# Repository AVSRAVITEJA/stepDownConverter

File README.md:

# stepDownConverter
In this project I have designed a DC-DC converter that steps down 48V to 28V, 12V and 5V. The pcb designed is used to distribute the input voltage to a camera, gimbal, flight controller and a radio. This pcb is a part of a high altitude surveillance drone with an endurance of 5hrs.
The pcb uses LM2596 IC and XL4015 IC to step down the voltages. Most of the components used are SMD.

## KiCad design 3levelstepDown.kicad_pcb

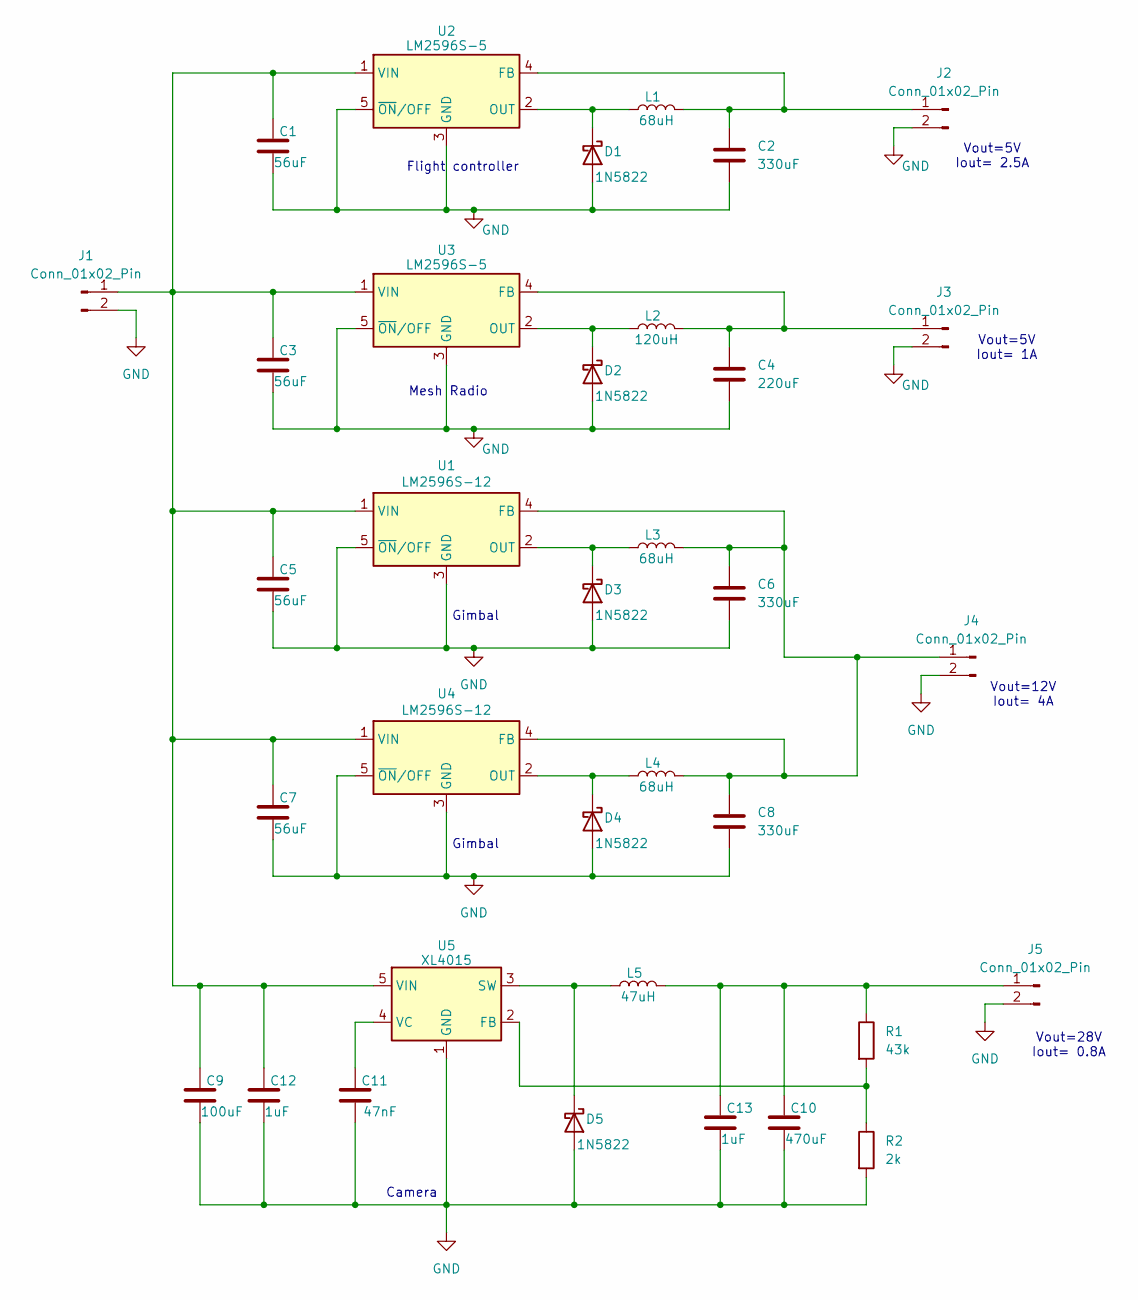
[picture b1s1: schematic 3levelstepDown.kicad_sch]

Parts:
C1, C3, C5, C7: 56uF; CP_Elec_6.3x5.8
C2, C6, C8: 330uF; CP_Elec_6.3x7.7
C4: 220uF; CP_Elec_6.3x5.8
C9: 100uF; CP_Elec_6.3x7.7
C10: 470uF; CP_Elec_8x10.5
C11: 47nF; C_0603_1608Metric
C12, C13: 1uF; C_0805_2012Metric
D1, D2, D3, D4, D5: 1N5822; D_1206_3216Metric_Pad1.42x1.75mm_HandSolder
J1, J2, J3, J4, J5: Conn_01x02_Pin; AMASS_XT60-M_1x02_P7.20mm_Vertical
L1, L3, L4: 68uH; L_0201_0603Metric
L2: 120uH; L_0201_0603Metric
L5: 47uH; L_0201_0603Metric
R1: 43k; R_0201_0603Metric
R2: 2k; R_0201_0603Metric
U1, U4: LM2596S-12; TO-263-5_TabPin3
U2, U3: LM2596S-5; TO-263-5_TabPin3
U5: XL4015; TO-263-5_TabPin3

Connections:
GND: C1.2, C2.2, C3.2, C4.2, C5.2, C6.2, C7.2, C8.2, C9.2, C10.2, C11.2, C12.2, C13.2, D1.2 (A), D2.2 (A), D3.2 (A), D4.2 (A), D5.2 (A), J1.2, J2.2, J3.2, J4.2, J5.2, R2.2, U1.3 (GND), U1.5 (~ON/OFF), U2.3 (GND), U2.5 (~ON/OFF), U3.3 (GND), U3.5 (~ON/OFF), U4.3 (GND), U4.5 (~ON/OFF), U5.1 (GND)
unnamed: D1.1 (K), L1.1, U2.2 (OUT)
unnamed: D2.1 (K), L2.1, U3.2 (OUT)
unnamed: D3.1 (K), L3.1, U1.2 (OUT)
unnamed: D4.1 (K), L4.1, U4.2 (OUT)
unnamed: D5.1 (K), L5.1, U5.3 (SW)
unnamed: C1.1, C3.1, C5.1, C7.1, C9.1, C12.1, J1.1, U1.1 (VIN), U2.1 (VIN), U3.1 (VIN), U4.1 (VIN), U5.5 (VIN)
unnamed: C2.1, J2.1, L1.2, U2.4 (FB)
unnamed: C4.1, J3.1, L2.2, U3.4 (FB)
unnamed: C6.1, C8.1, J4.1, L3.2, L4.2, U1.4 (FB), U4.4 (FB)
unnamed: C10.1, C13.1, J5.1, L5.2, R1.1
unnamed: R1.2, R2.1, U5.2 (FB)
unnamed: C11.1, U5.4 (VC)

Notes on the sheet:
Gimbal
Camera
Vout=5V Iout= 2.5A
Mesh Radio
Flight controller
Vout=5V Iout= 1A
Vout=28V Iout= 0.8A
Vout=12V Iout= 4A

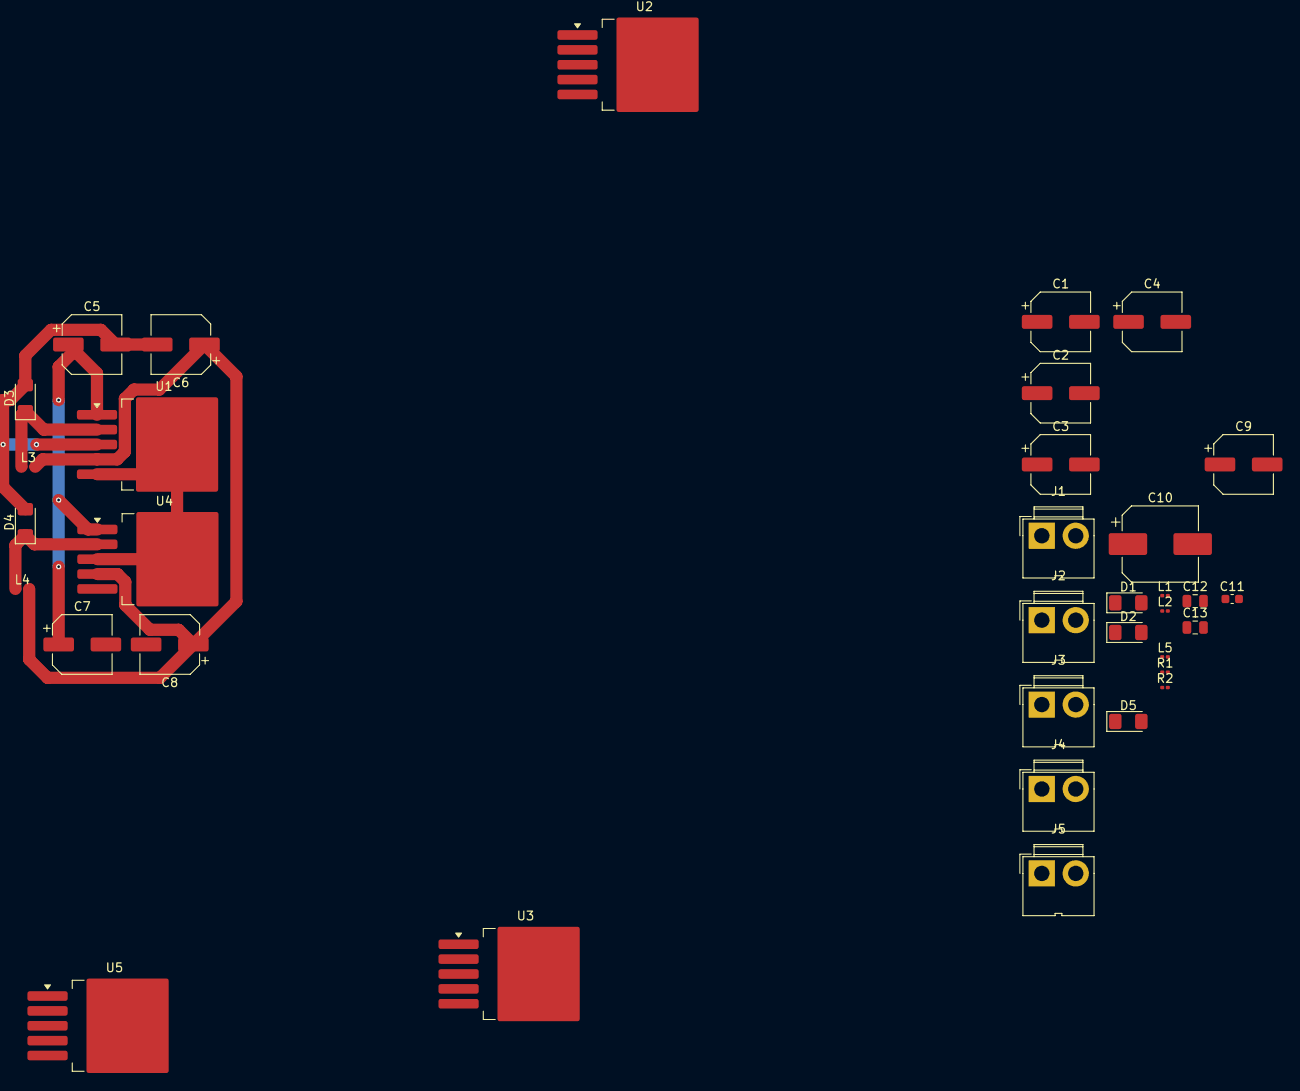
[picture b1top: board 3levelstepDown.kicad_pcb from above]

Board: 2 copper layers, 35 parts (0 on the bottom side), 13 nets.
